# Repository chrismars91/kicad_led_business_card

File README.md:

https://www.instructables.com/LED-MATTiny-rix-Business-Card-With-the-HT16K33A/

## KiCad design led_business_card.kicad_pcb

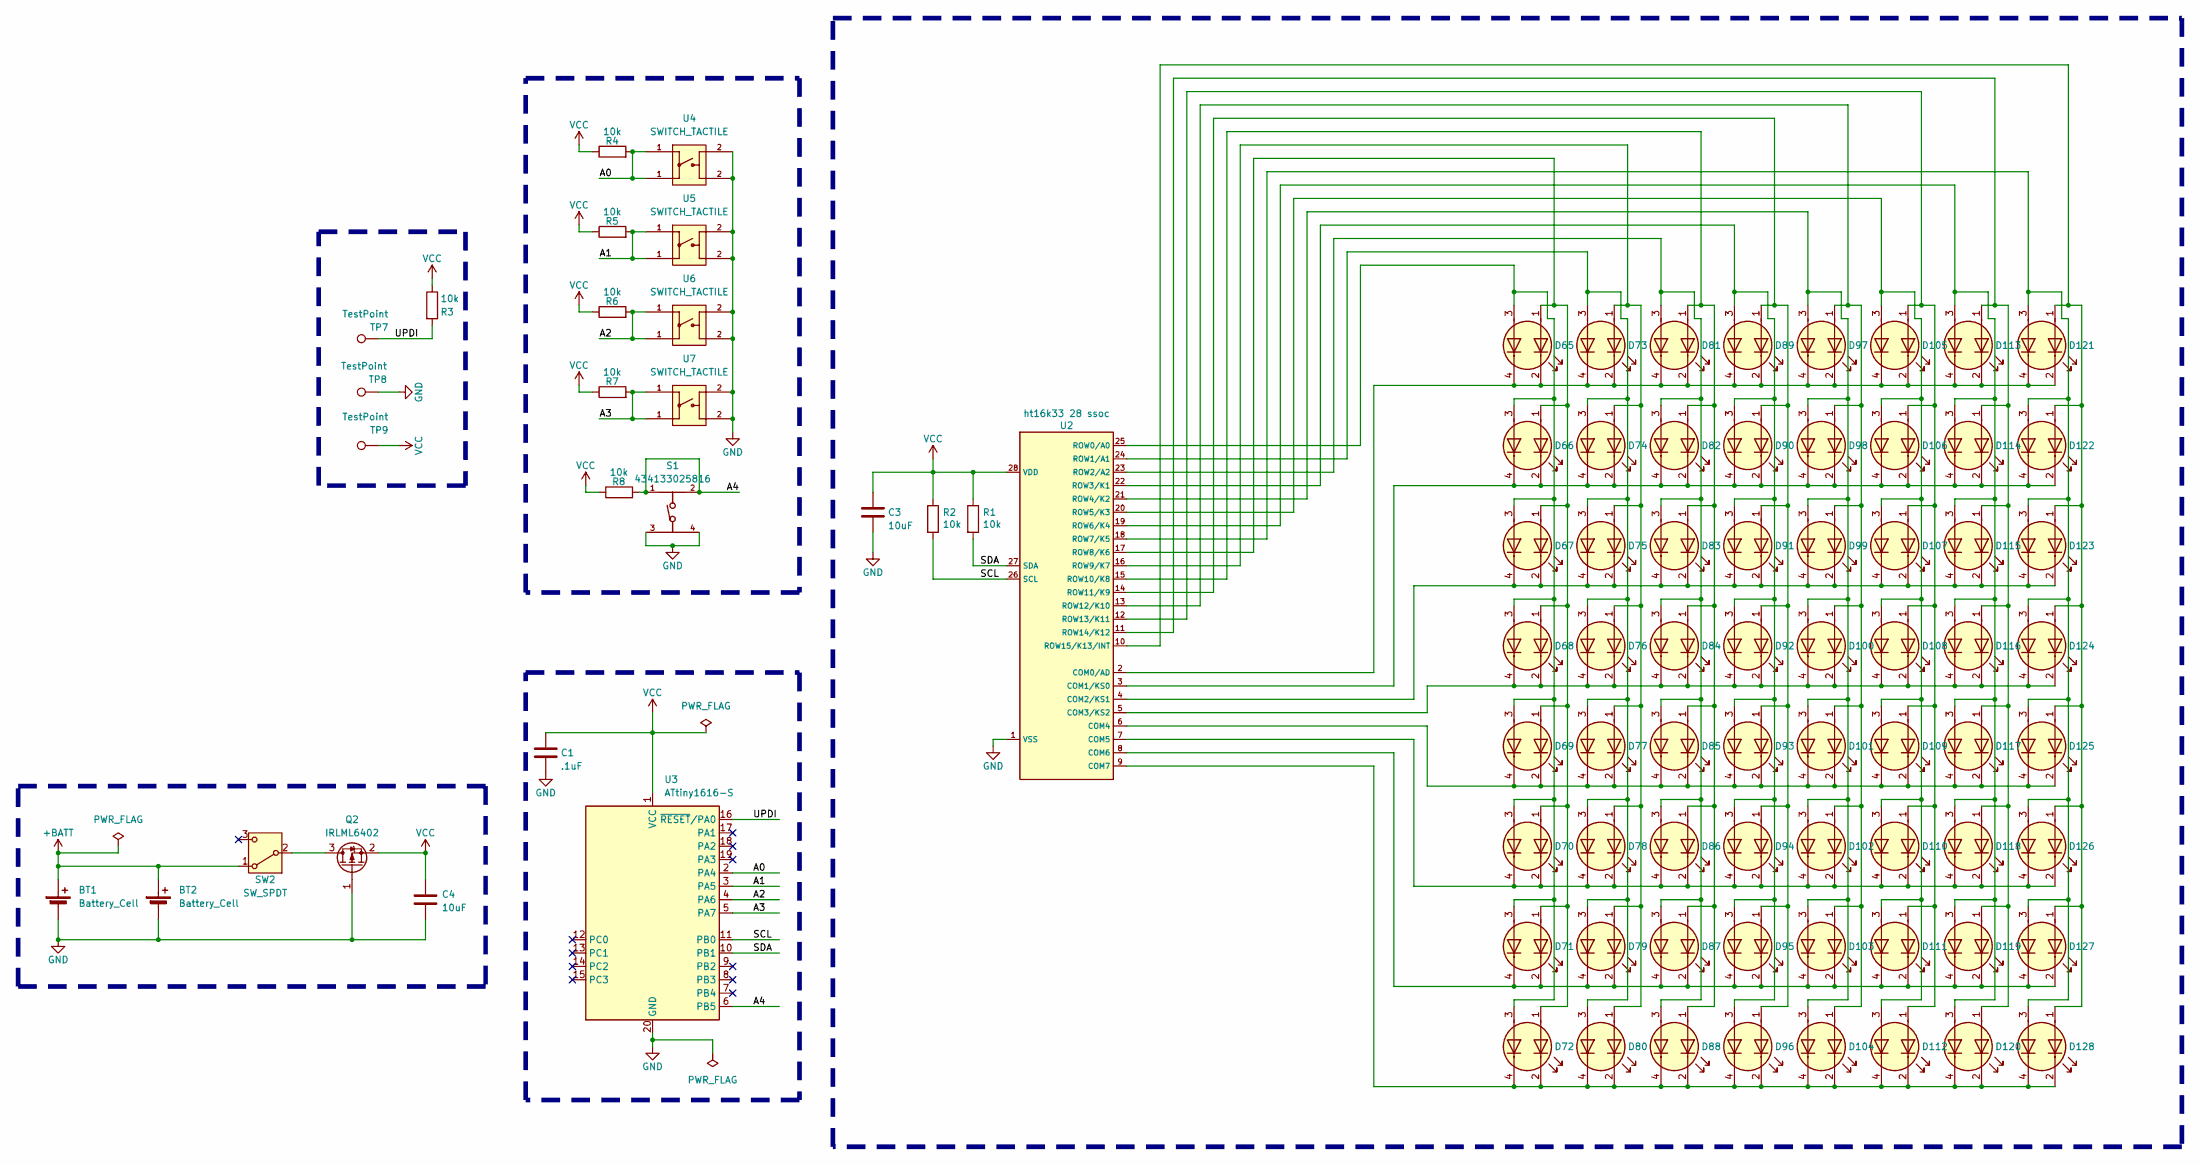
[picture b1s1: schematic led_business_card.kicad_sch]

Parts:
BT1, BT2: Battery_Cell; BAT_3002
C1: .1uF; C_0603_1608Metric
C3, C4: 10uF; C_0603_1608Metric
D65, D66, D67, D68, D69, D70, D71, D72, D73, D74, D75, D76, D77, D78, D79, D80, D81, D82, D83, D84, D85, D86, D87, D88, D89, D90, D91, D92, D93, D94, D95, D96, D97, D98, D99, D100, D101, D102, D103, D104, D105, D106, D107, D108, D109, D110, D111, D112, D113, D114, D115, D116, D117, D118, D119, D120, D121, D122, D123, D124, D125, D126, D127, D128: LTST-BILED-15X16
Q2: IRLML6402; SOT-23
R1, R2, R3, R4, R5, R6, R7, R8: 10k; R_0603_1608Metric
S1: 434133025816
SW2: SW_SPDT; slide_switch_wurth
TP7, TP8, TP9: TestPoint; TestPoint_Pad_2.0x2.0mm
U2: ht16k33 28 ssoc; HT16K33_ssop
U3: ATtiny1616-S; SOIC-20W_7.5x12.8mm_P1.27mm
U4, U5, U6, U7: SWITCH_TACTILE; button_6mm_smd

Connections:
+BATT: BT1.1 (+), BT2.1 (+), SW2.1 (A)
/A0: R4.2, U3.2 (PA4), U4.1
/A1: R5.2, U3.3 (PA5), U5.1
/A2: R6.2, U3.4 (PA6), U6.1
/A3: R7.2, U3.5 (PA7), U7.1
/A4: R8.2, S1.1, S1.2, U3.6 (PB5)
/SCL: R2.2, U2.26 (SCL), U3.11 (PB0)
/SDA: R1.2, U2.27 (SDA), U3.10 (PB1)
/UPDI: R3.2, TP7.1, U3.16 (~RESET/PA0)
GND: BT1.2 (-), BT2.2 (-), C1.2, C3.2, C4.2, Q2.1 (G), S1.3, S1.4, TP8.1, U2.1 (VSS), U3.20 (GND), U4.2, U5.2, U6.2, U7.2
unnamed: D65.1 (A1), D66.1 (A1), D67.1 (A1), D68.1 (A1), D69.1 (A1), D70.1 (A1), D71.1 (A1), D72.1 (A1), U2.17 (ROW8/K6)
unnamed: D65.3 (A2), D66.3 (A2), D67.3 (A2), D68.3 (A2), D69.3 (A2), D70.3 (A2), D71.3 (A2), D72.3 (A2), U2.25 (ROW0/A0)
unnamed: D73.1 (A1), D74.1 (A1), D75.1 (A1), D76.1 (A1), D77.1 (A1), D78.1 (A1), D79.1 (A1), D80.1 (A1), U2.16 (ROW9/K7)
unnamed: D73.3 (A2), D74.3 (A2), D75.3 (A2), D76.3 (A2), D77.3 (A2), D78.3 (A2), D79.3 (A2), D80.3 (A2), U2.24 (ROW1/A1)
unnamed: D81.1 (A1), D82.1 (A1), D83.1 (A1), D84.1 (A1), D85.1 (A1), D86.1 (A1), D87.1 (A1), D88.1 (A1), U2.15 (ROW10/K8)
unnamed: D81.3 (A2), D82.3 (A2), D83.3 (A2), D84.3 (A2), D85.3 (A2), D86.3 (A2), D87.3 (A2), D88.3 (A2), U2.23 (ROW2/A2)
unnamed: D89.1 (A1), D90.1 (A1), D91.1 (A1), D92.1 (A1), D93.1 (A1), D94.1 (A1), D95.1 (A1), D96.1 (A1), U2.14 (ROW11/K9)
unnamed: D89.3 (A2), D90.3 (A2), D91.3 (A2), D92.3 (A2), D93.3 (A2), D94.3 (A2), D95.3 (A2), D96.3 (A2), U2.22 (ROW3/K1)
unnamed: D97.1 (A1), D98.1 (A1), D99.1 (A1), D100.1 (A1), D101.1 (A1), D102.1 (A1), D103.1 (A1), D104.1 (A1), U2.13 (ROW12/K10)
unnamed: D97.3 (A2), D98.3 (A2), D99.3 (A2), D100.3 (A2), D101.3 (A2), D102.3 (A2), D103.3 (A2), D104.3 (A2), U2.21 (ROW4/K2)
unnamed: D68.2 (K1), D68.4 (K2), D76.2 (K1), D76.4 (K2), D84.2 (K1), D84.4 (K2), D92.2 (K1), D92.4 (K2), D100.2 (K1), D100.4 (K2), D108.2 (K1), D108.4 (K2), D116.2 (K1), D116.4 (K2), D124.2 (K1), D124.4 (K2), U2.5 (COM3/KS2)
unnamed: D69.2 (K1), D69.4 (K2), D77.2 (K1), D77.4 (K2), D85.2 (K1), D85.4 (K2), D93.2 (K1), D93.4 (K2), D101.2 (K1), D101.4 (K2), D109.2 (K1), D109.4 (K2), D117.2 (K1), D117.4 (K2), D125.2 (K1), D125.4 (K2), U2.6 (COM4)
unnamed: D70.2 (K1), D70.4 (K2), D78.2 (K1), D78.4 (K2), D86.2 (K1), D86.4 (K2), D94.2 (K1), D94.4 (K2), D102.2 (K1), D102.4 (K2), D110.2 (K1), D110.4 (K2), D118.2 (K1), D118.4 (K2), D126.2 (K1), D126.4 (K2), U2.7 (COM5)
unnamed: D71.2 (K1), D71.4 (K2), D79.2 (K1), D79.4 (K2), D87.2 (K1), D87.4 (K2), D95.2 (K1), D95.4 (K2), D103.2 (K1), D103.4 (K2), D111.2 (K1), D111.4 (K2), D119.2 (K1), D119.4 (K2), D127.2 (K1), D127.4 (K2), U2.8 (COM6)
unnamed: D72.2 (K1), D72.4 (K2), D80.2 (K1), D80.4 (K2), D88.2 (K1), D88.4 (K2), D96.2 (K1), D96.4 (K2), D104.2 (K1), D104.4 (K2), D112.2 (K1), D112.4 (K2), D120.2 (K1), D120.4 (K2), D128.2 (K1), D128.4 (K2), U2.9 (COM7)
unnamed: D105.1 (A1), D106.1 (A1), D107.1 (A1), D108.1 (A1), D109.1 (A1), D110.1 (A1), D111.1 (A1), D112.1 (A1), U2.12 (ROW13/K11)
unnamed: D105.3 (A2), D106.3 (A2), D107.3 (A2), D108.3 (A2), D109.3 (A2), D110.3 (A2), D111.3 (A2), D112.3 (A2), U2.20 (ROW5/K3)
unnamed: D65.2 (K1), D65.4 (K2), D73.2 (K1), D73.4 (K2), D81.2 (K1), D81.4 (K2), D89.2 (K1), D89.4 (K2), D97.2 (K1), D97.4 (K2), D105.2 (K1), D105.4 (K2), D113.2 (K1), D113.4 (K2), D121.2 (K1), D121.4 (K2), U2.2 (COM0/AD)
unnamed: D66.2 (K1), D66.4 (K2), D74.2 (K1), D74.4 (K2), D82.2 (K1), D82.4 (K2), D90.2 (K1), D90.4 (K2), D98.2 (K1), D98.4 (K2), D106.2 (K1), D106.4 (K2), D114.2 (K1), D114.4 (K2), D122.2 (K1), D122.4 (K2), U2.3 (COM1/KS0)
unnamed: D67.2 (K1), D67.4 (K2), D75.2 (K1), D75.4 (K2), D83.2 (K1), D83.4 (K2), D91.2 (K1), D91.4 (K2), D99.2 (K1), D99.4 (K2), D107.2 (K1), D107.4 (K2), D115.2 (K1), D115.4 (K2), D123.2 (K1), D123.4 (K2), U2.4 (COM2/KS1)
unnamed: D113.1 (A1), D114.1 (A1), D115.1 (A1), D116.1 (A1), D117.1 (A1), D118.1 (A1), D119.1 (A1), D120.1 (A1), U2.11 (ROW14/K12)
unnamed: D113.3 (A2), D114.3 (A2), D115.3 (A2), D116.3 (A2), D117.3 (A2), D118.3 (A2), D119.3 (A2), D120.3 (A2), U2.19 (ROW6/K4)
unnamed: D121.1 (A1), D122.1 (A1), D123.1 (A1), D124.1 (A1), D125.1 (A1), D126.1 (A1), D127.1 (A1), D128.1 (A1), U2.10 (ROW15/K13/INT)
unnamed: D121.3 (A2), D122.3 (A2), D123.3 (A2), D124.3 (A2), D125.3 (A2), D126.3 (A2), D127.3 (A2), D128.3 (A2), U2.18 (ROW7/K5)
unnamed: Q2.3 (D), SW2.2 (B)
VCC: C1.1, C3.1, C4.1, Q2.2 (S), R1.1, R2.1, R3.1, R4.1, R5.1, R6.1, R7.1, R8.1, TP9.1, U2.28 (VDD), U3.1 (VCC)

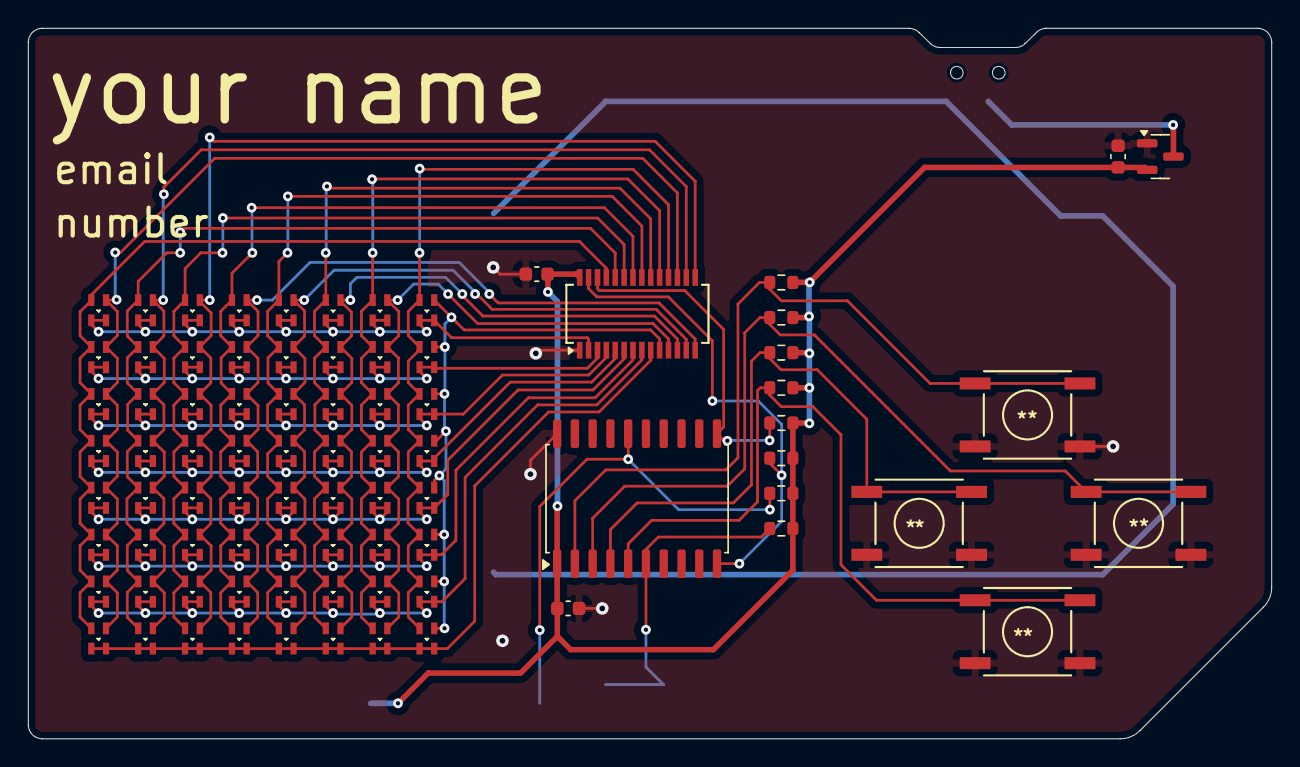
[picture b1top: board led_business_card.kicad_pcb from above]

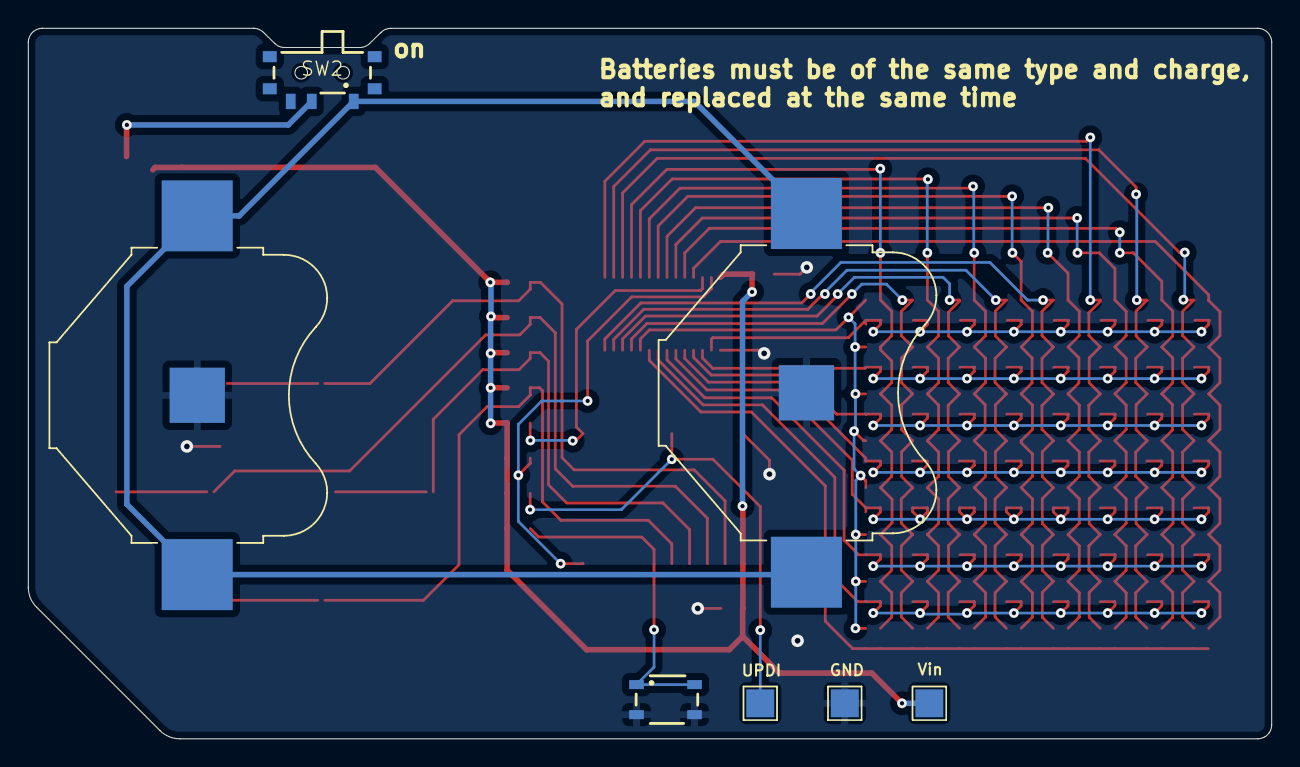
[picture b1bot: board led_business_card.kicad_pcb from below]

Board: 2 copper layers, 88.9 x 50.8 mm, 89 parts (7 on the bottom side), 36 nets.

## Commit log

2025-04-23 init
2025-04-23 added flappy bird code
